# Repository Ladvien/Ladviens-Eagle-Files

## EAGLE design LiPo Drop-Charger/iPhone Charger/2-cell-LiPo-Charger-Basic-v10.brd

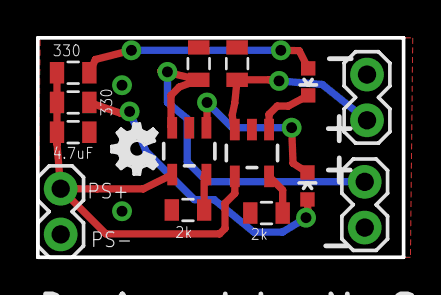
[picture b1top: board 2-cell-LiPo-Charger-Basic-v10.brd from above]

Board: 2 copper layers, 20.3 x 12.2 mm, 16 parts (0 on the bottom side), 10 nets.

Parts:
C1, C3, C4: 4.7uF; 0805
D1, D11: RED; LED-0603
JP1, JP2, JP3: 1X02
R1, R3: 330; 0805
R2, R4: 2K; 0805
U1, U2: MCP73831; SOT23-5
U$2: BAND_LOGO_SMALL
U$3: OSHW_FILLX100_NOTEXT

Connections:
GND: C1.2, C3.2, C4.2, JP1.1, JP2.1, JP3.2, R2.2, R4.2, U1.2, U2.2
unnamed: D1.A, R1.1
unnamed: D11.A, R3.1
PROG: R4.1, U1.5
PROG1: R2.1, U2.5
STAT: D11.C, U1.1
STAT1: D1.C, U2.1
VCC: C4.1, JP1.2, U1.3
VCC2: C1.1, JP2.2, U2.3
VIN: C3.1, JP3.1, R1.2, R3.2, U1.4, U2.4

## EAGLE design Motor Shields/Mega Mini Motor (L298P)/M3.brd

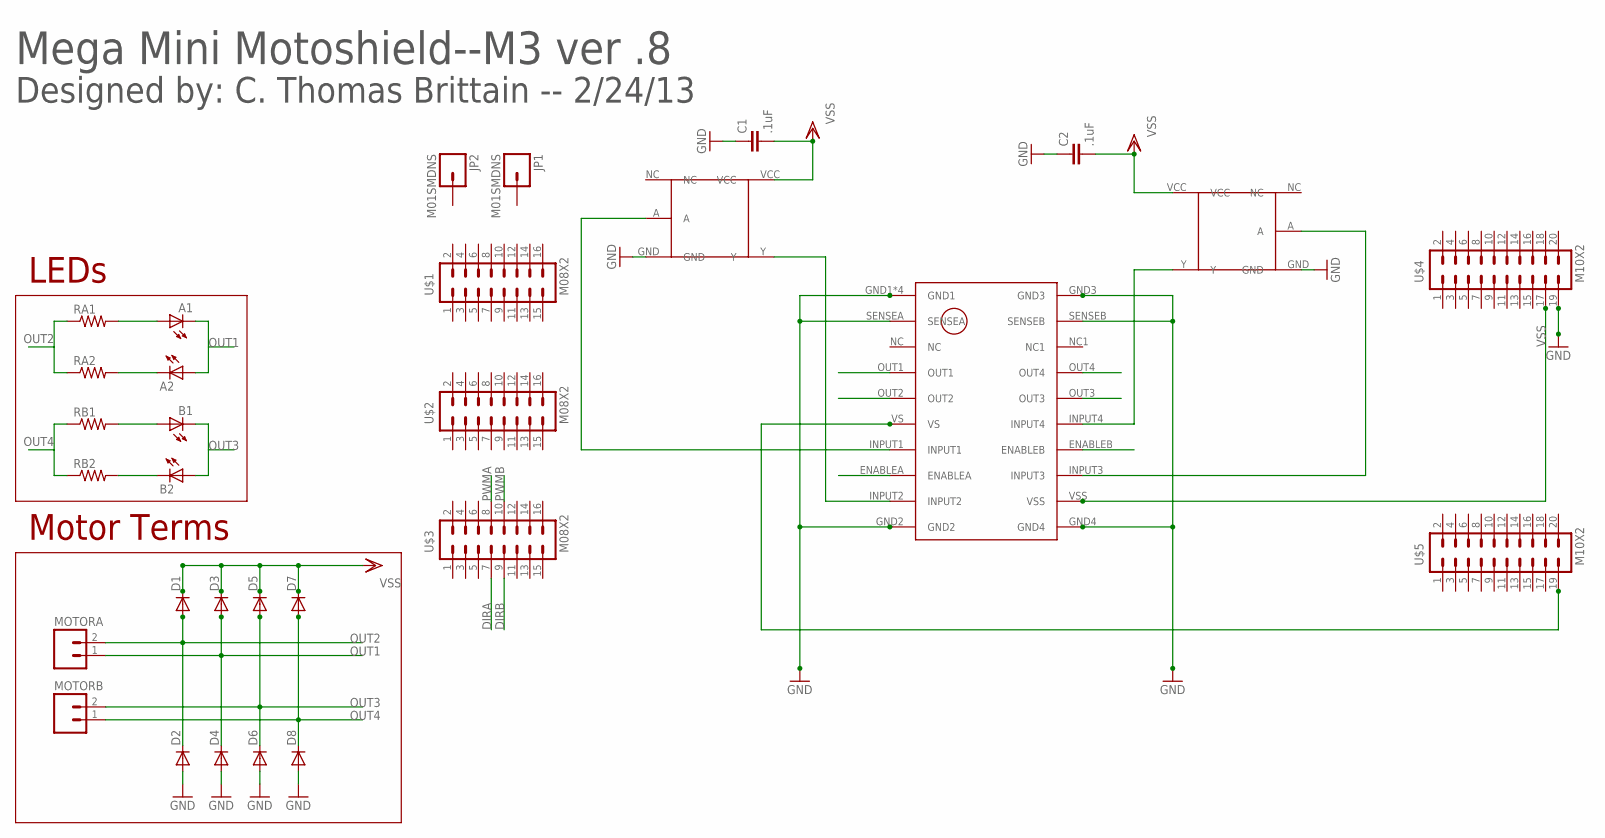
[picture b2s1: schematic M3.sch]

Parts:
A1, A2: LEDSML0603; SML0603
B1, B2: LEDSML0603; SML0603
C1, C2: .1uF; C0805
D1, D2, D3, D4, D5, D6, D7, D8: DIODESMA; SMA-DIODE
JP1, JP2: M01SMDNS; 1X01NS
MOTORA: M023.5MM; SCREWTERMINAL-3.5MM-2
MOTORB: M023.5MM; SCREWTERMINAL-3.5MM-2
RA1, RA2: R-US_R0805; R0805
RB1, RB2: R-US_R0805; R0805
U$1, U$2, U$3: M08X2; 2X8
U$4, U$5: M10X2; 2X10
U$6: L298P; SMARTPRJ_POWER-SO20
U$7, U$8: 74HC1G04; SPARKFUN_SC70

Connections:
DIRA: U$3.7, U$6.INPUT1, U$7.A
DIRB: U$3.9, U$6.INPUT3, U$8.A
GND: C1.1, C2.1, D2.A, D4.A, D6.A, D8.A, U$4.19, U$6.GND1, U$6.GND2, U$6.GND3, U$6.GND4, U$6.GND5 (GND1), U$6.GND6 (GND1), U$6.GND7 (GND1), U$6.SENSEA, U$6.SENSEB, U$7.GND, U$8.GND
unnamed: A2.C, RA2.2
unnamed: U$5.19, U$6.VS
unnamed: U$6.INPUT2, U$7.Y
unnamed: U$6.INPUT4, U$8.Y
unnamed: A1.A, RA1.2
unnamed: B1.A, RB1.2
unnamed: B2.C, RB2.2
OUT1: A1.C, A2.A, D3.A, D4.C, MOTORA.1, U$6.OUT1
OUT2: D1.A, D2.C, MOTORA.2, RA1.1, RA2.1, U$6.OUT2
OUT3: B1.C, B2.A, D5.A, D6.C, MOTORB.2, U$6.OUT4
OUT4: D7.A, D8.C, MOTORB.1, RB1.1, RB2.1, U$6.OUT3
PWMA: U$3.8, U$6.ENABLEA
PWMB: U$3.10, U$6.ENABLEB
VSS: C1.2, C2.2, D1.C, D3.C, D5.C, D7.C, U$4.17, U$6.VSS, U$7.VCC, U$8.VCC

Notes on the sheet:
Motor Terms
Mega Mini Motoshield--M3 ver .8
Designed by: C. Thomas Brittain -- 2/24/13
LEDs

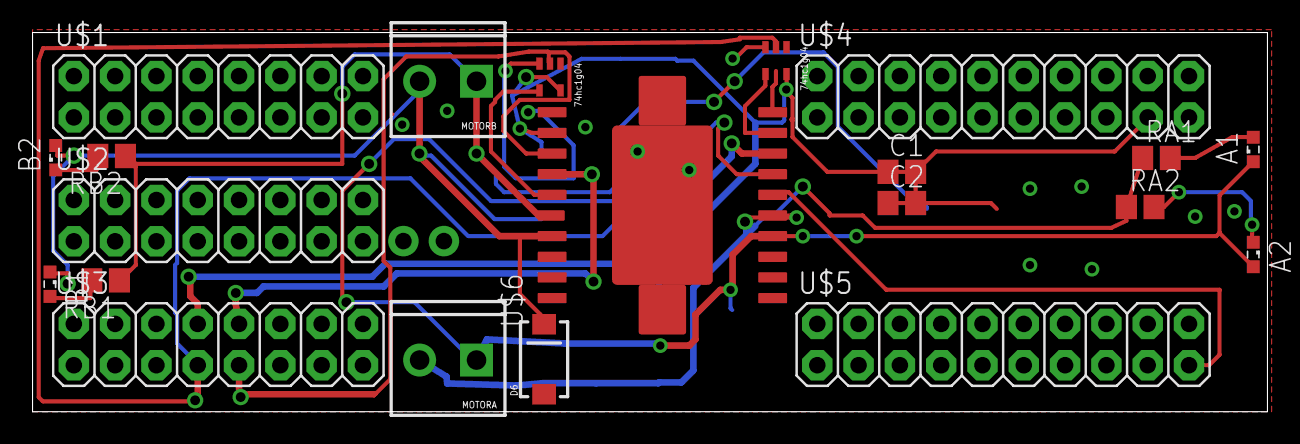
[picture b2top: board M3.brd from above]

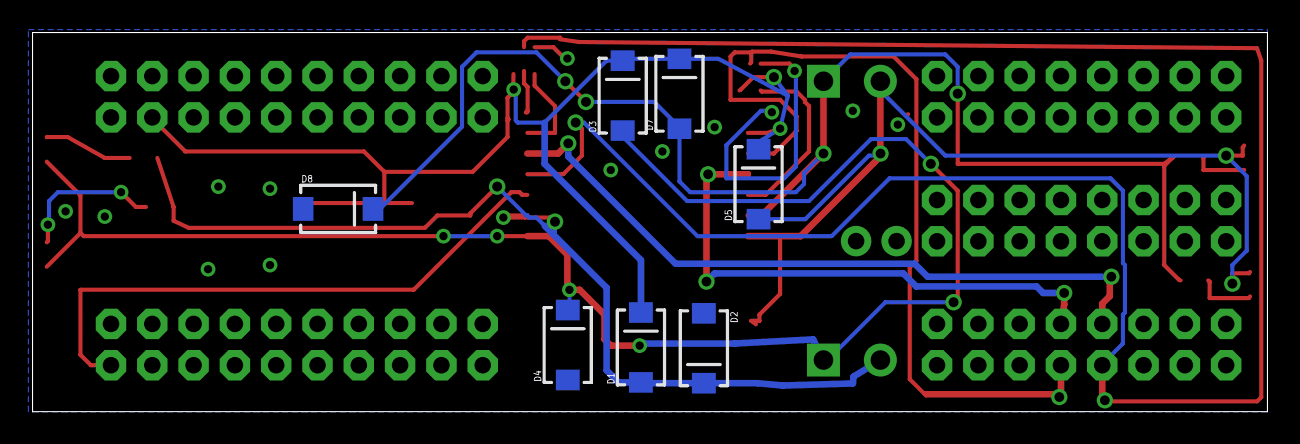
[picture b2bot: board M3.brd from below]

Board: 2 copper layers, 75.9 x 23.3 mm, 30 parts (7 on the bottom side), 17 nets.

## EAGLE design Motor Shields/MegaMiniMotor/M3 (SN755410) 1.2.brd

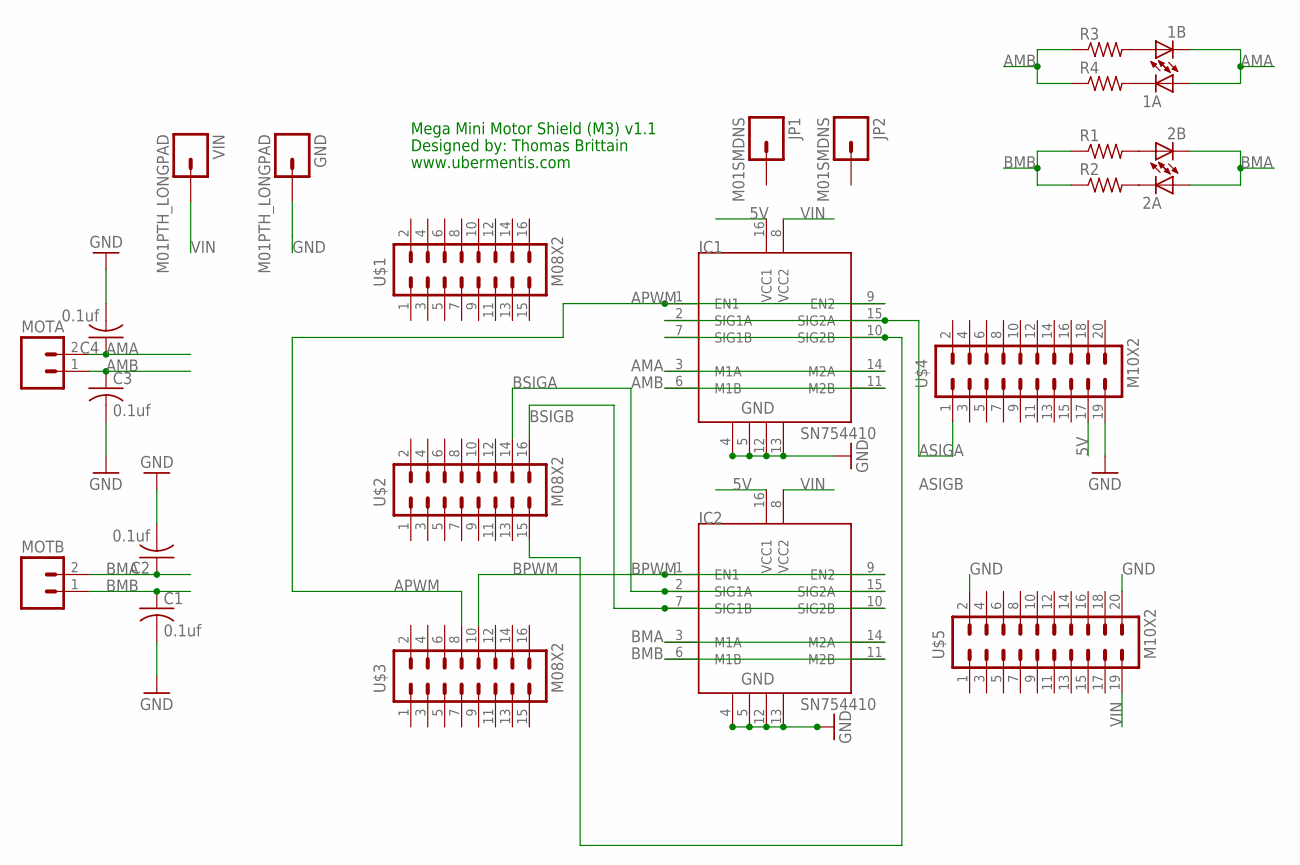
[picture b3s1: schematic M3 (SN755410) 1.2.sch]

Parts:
1A, 1B, 2A, 2B: LEDSML0603; SML0603
C1, C2, C3, C4: 0.1uf; C0805
GND: M01PTH_LONGPAD; 1X01_LONGPAD
IC1, IC2: SN754410; DIP16
JP1, JP2: M01SMDNS; 1X01NS
MOTA: M021X02_NO_SILK; 1X02_NO_SILK
MOTB: M021X02_NO_SILK; 1X02_NO_SILK
R1, R2, R3, R4: R-US_R0805; R0805
U$1, U$2, U$3: M08X2; 2X8
U$4, U$5: M10X2; 2X10
VIN: M01PTH_LONGPAD; 1X01_LONGPAD

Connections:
5V: IC1.16 (VCC1), IC2.16 (VCC1), U$4.17
AMA: 1A.A, 1B.C, C4.1, IC1.3 (M1A), IC1.14 (M2A), MOTA.2
AMB: C3.1, IC1.6 (M1B), IC1.11 (M2B), MOTA.1, R3.1, R4.1
APWM: IC1.1 (EN1), IC1.9 (EN2), U$3.8
ASIGA: IC1.2 (SIG1A), IC1.15 (SIG2A), U$4.1
ASIGB: IC1.7 (SIG1B), IC1.10 (SIG2B), U$2.15
BMA: 2A.A, 2B.C, C2.1, IC2.3 (M1A), IC2.14 (M2A), MOTB.2
BMB: C1.1, IC2.6 (M1B), IC2.11 (M2B), MOTB.1, R1.1, R2.1
BPWM: IC2.1 (EN1), IC2.9 (EN2), U$3.10
BSIGA: IC2.2 (SIG1A), IC2.15 (SIG2A), U$2.14
BSIGB: IC2.7 (SIG1B), IC2.10 (SIG2B), U$2.16
GND: C1.2, C2.2, C3.2, C4.2, GND.1, IC1.4, IC1.5, IC1.12, IC1.13, IC2.4, IC2.5, IC2.12, IC2.13, U$4.19, U$5.2, U$5.20
unnamed: 2B.A, R1.2
unnamed: 2A.C, R2.2
unnamed: 1B.A, R3.2
unnamed: 1A.C, R4.2
VIN: IC1.8 (VCC2), IC2.8 (VCC2), U$5.19, VIN.1

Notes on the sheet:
Mega Mini Motor Shield (M3) v1.1
Designed by: Thomas Brittain
www.ubermentis.com

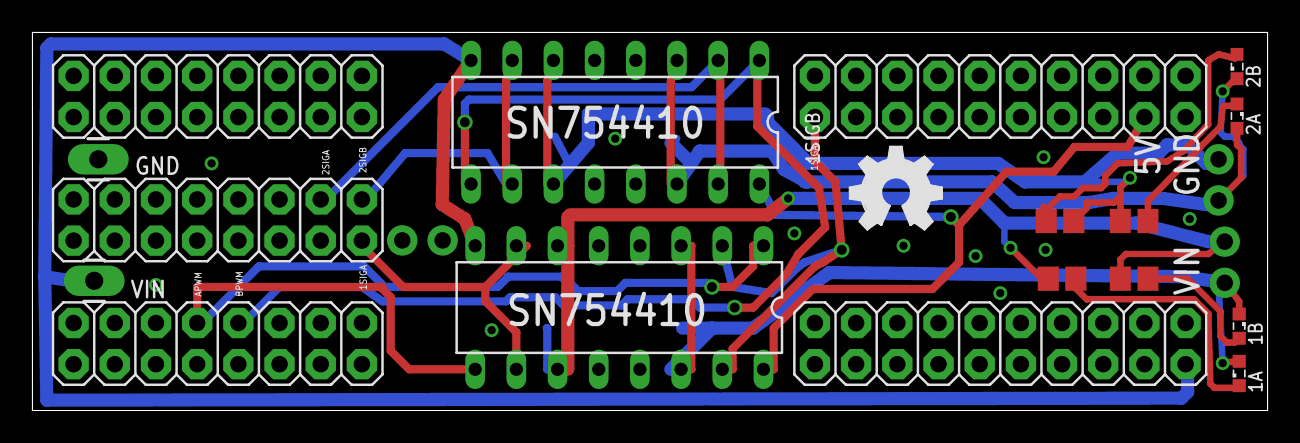
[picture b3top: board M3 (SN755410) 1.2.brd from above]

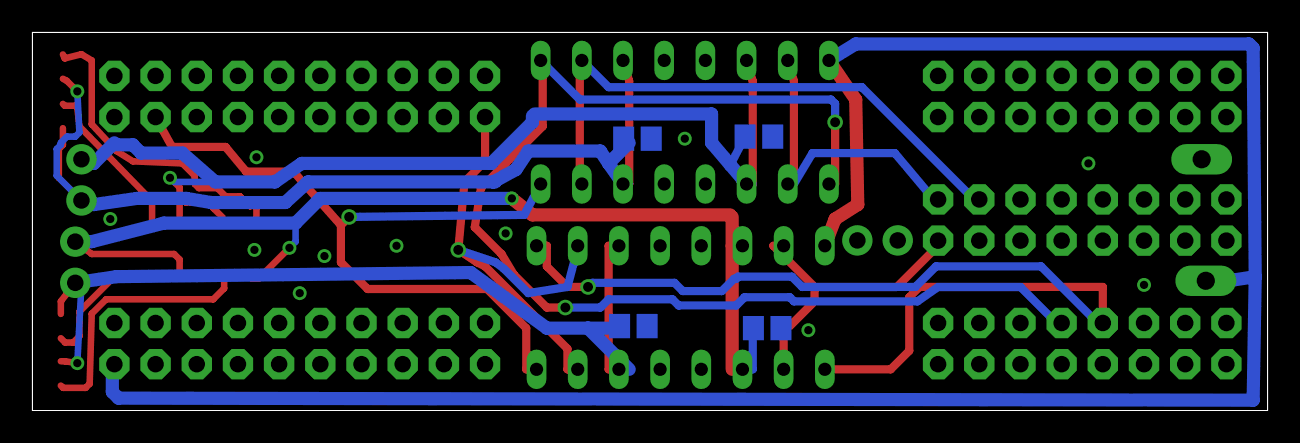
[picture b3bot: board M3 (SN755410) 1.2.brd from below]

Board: 2 copper layers, 76.2 x 23.3 mm, 26 parts (4 on the bottom side), 17 nets.

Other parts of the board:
U$7: OSHW_FILLX200_NOTEXT

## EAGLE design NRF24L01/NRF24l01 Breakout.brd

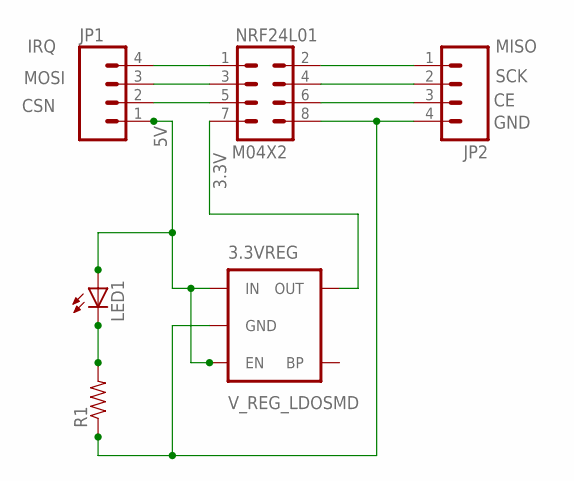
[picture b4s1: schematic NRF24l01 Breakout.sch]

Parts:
3.3VREG: V_REG_LDOSMD; SOT23-5
JP1, JP2: M04LOCK; 1X04_LOCK
LED1: LED0603; LED-0603
NRF24L01: M04X2; 2X4
R1: RESISTOR0805-RES; 0805

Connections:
3.3V: 3.3VREG.5 (OUT), NRF24L01.7
5V: 3.3VREG.1 (IN), 3.3VREG.3 (EN), JP1.1, LED1.A
CE: JP2.3, NRF24L01.6
CSN: JP1.2, NRF24L01.5
GND: 3.3VREG.2 (GND), JP2.4, NRF24L01.8, R1.1
IRQ: JP1.4, NRF24L01.1
MISO: JP2.1, NRF24L01.2
MOSI: JP1.3, NRF24L01.3
unnamed: LED1.C, R1.2
SCK: JP2.2, NRF24L01.4

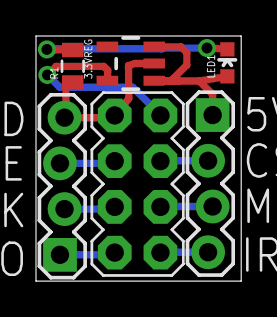
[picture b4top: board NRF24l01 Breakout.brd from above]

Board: 2 copper layers, 11.4 x 13.6 mm, 7 parts (1 on the bottom side), 10 nets.

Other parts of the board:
U$1: OSHW_FILLX100_NOTEXT

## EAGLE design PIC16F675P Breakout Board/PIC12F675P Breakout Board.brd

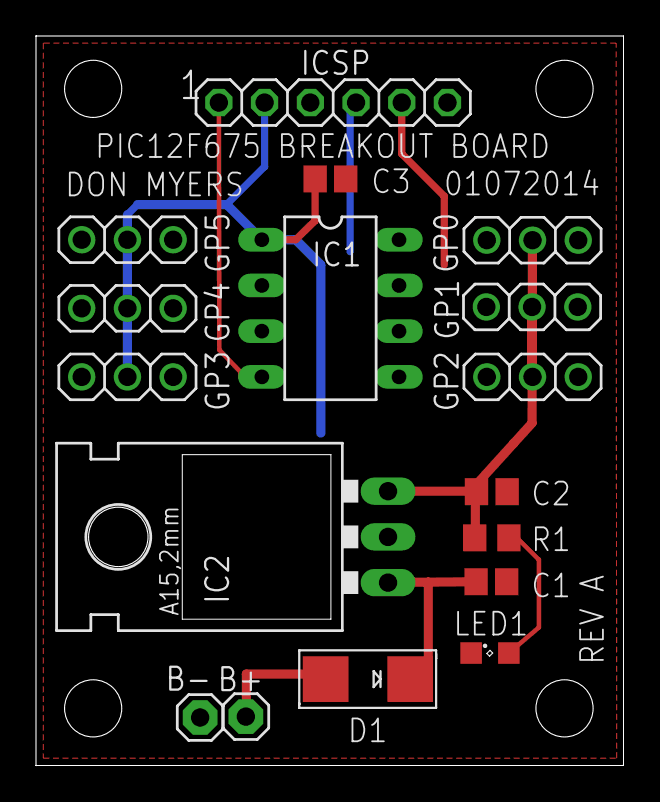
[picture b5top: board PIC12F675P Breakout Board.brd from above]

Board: 2 copper layers, 32.6 x 40.5 mm, 17 parts (0 on the bottom side), 10 nets.

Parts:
B+: 1X01
B-: 1X01
C1, C3: .1uF; C0805
C2: 1uF; C0805
D1: SMADIODE
GP0, GP1, GP2, GP3, GP4, GP5: 1X03
IC1: PIC12F675P; DIL8
IC2: 78XXL
ICSP: 1X06
LED1: SML0805
R1: 330; R0805

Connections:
GND: B-.1, C1.2, C2.2, C3.2, GP0.1, GP1.1, GP2.1, GP3.3, GP4.3, GP5.3, IC1.8, IC2.GND, ICSP.3, LED1.C
GP2: GP2.3, IC1.5
GP4: GP4.1, IC1.3
GP5: GP5.1, IC1.2
unnamed: B+.1, D1.A
unnamed: LED1.A, R1.2
unnamed: C1.1, D1.C, IC2.IN
PGC: GP0.3, GP1.3, IC1.6, IC1.7, ICSP.5
VDD: C2.1, C3.1, GP0.2, GP1.2, GP2.2, GP3.2, GP4.2, GP5.2, IC1.1, IC2.OUT, ICSP.2, R1.1
VPP: GP3.1, IC1.4, ICSP.1

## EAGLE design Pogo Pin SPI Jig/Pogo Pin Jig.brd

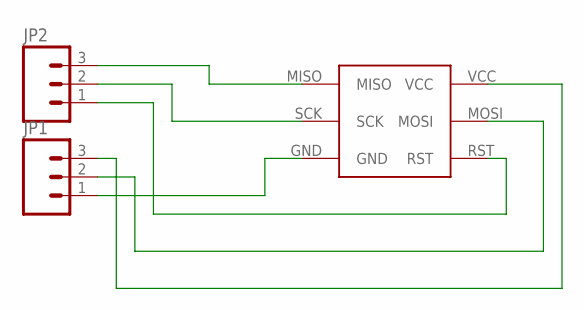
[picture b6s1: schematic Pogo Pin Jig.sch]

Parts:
JP1, JP2: M03PTH; 1X03
U$1: POGO_PIN_JIG_SPI

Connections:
unnamed: JP1.1, U$1.GND
unnamed: JP1.2, U$1.MOSI
unnamed: JP1.3, U$1.VCC
unnamed: JP2.3, U$1.MISO
unnamed: JP2.2, U$1.SCK
unnamed: JP2.1, U$1.RST

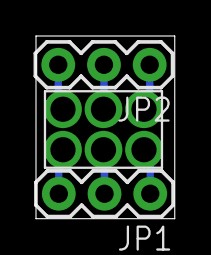
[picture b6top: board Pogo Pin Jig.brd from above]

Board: 2 copper layers, 7.7 x 10.2 mm, 3 parts (0 on the bottom side), 6 nets.

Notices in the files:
parts and their libraries:
SparkFun: Licensing: CC v3.0 Share-Alike You are welcome to use this library for commercial purposes.
